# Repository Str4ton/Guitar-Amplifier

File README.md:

# Guitar-Amplifier
A guitar amplifier using the TDA2030 IC and a pre-amp using uA741CN

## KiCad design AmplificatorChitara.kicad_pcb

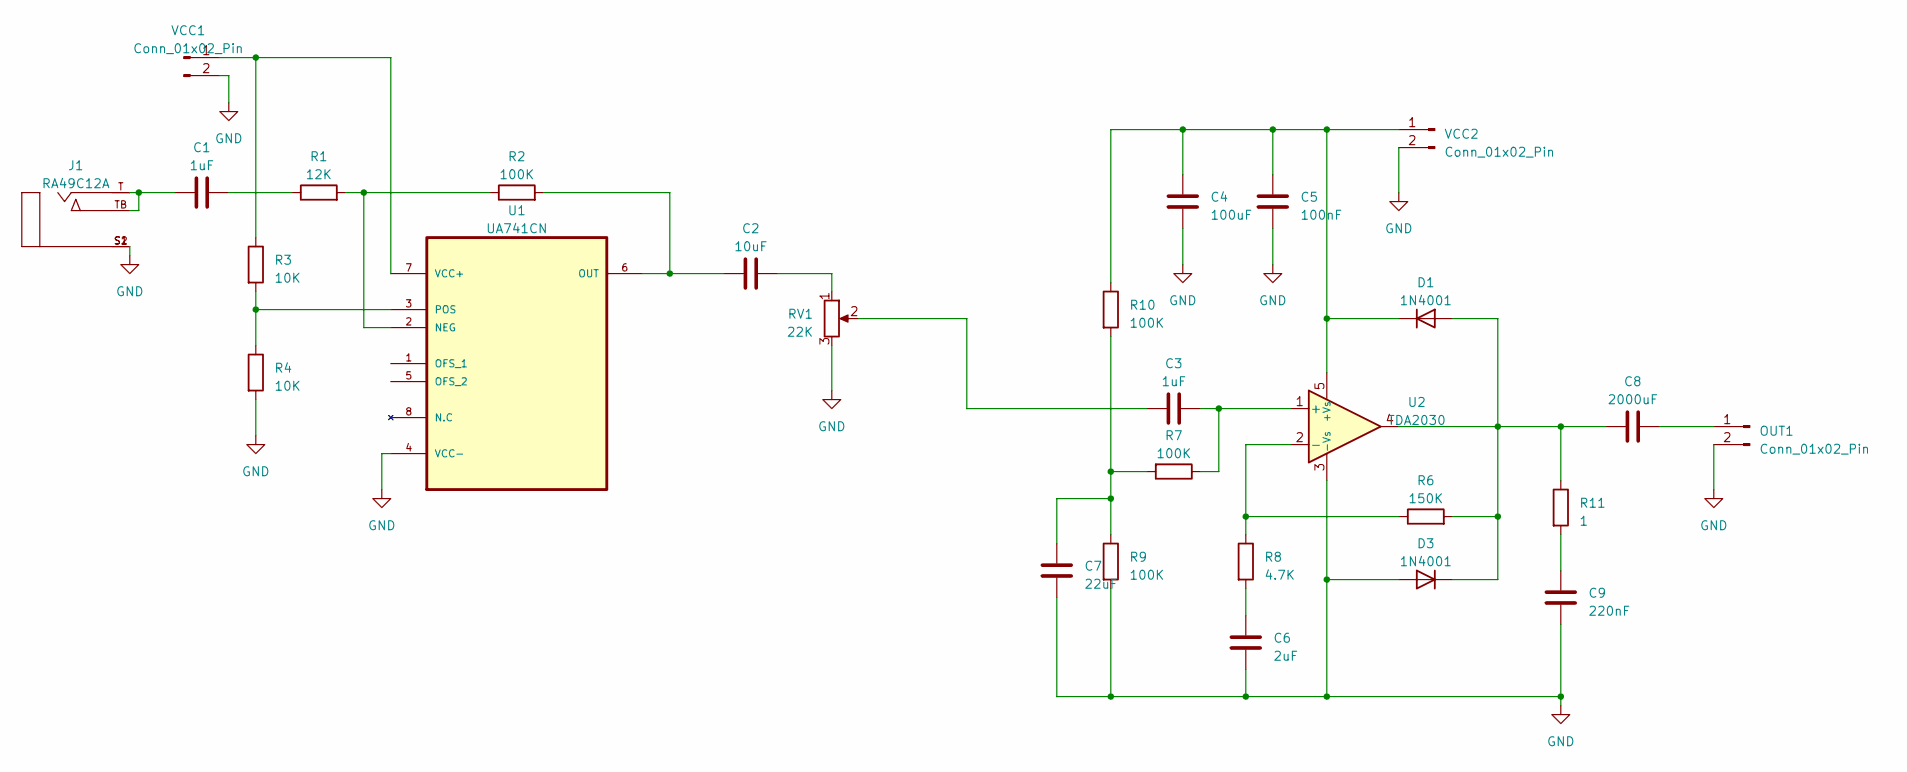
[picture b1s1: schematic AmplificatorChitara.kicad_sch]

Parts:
C1, C3: 1uF; CP_Radial_D10.0mm_P3.50mm
C2: 10uF; CP_Radial_D10.0mm_P3.50mm
C4: 100uF; CP_Radial_D10.0mm_P3.50mm
C5: 100nF; CP_Radial_D10.0mm_P3.50mm
C6: 2uF; CP_Radial_D10.0mm_P3.50mm
C7: 22uF; CP_Radial_D10.0mm_P3.50mm
C8: 2000uF; CP_Radial_D10.0mm_P3.50mm
C9: 220nF; CP_Radial_D10.0mm_P3.50mm
D1, D3: 1N4001; D_DO-41_SOD81_P10.16mm_Horizontal
J1: RA49C12A; SWITCHCRAFT_RA49C12A; PARTREV F
OUT1: Conn_01x02_Pin; TerminalBlock_4Ucon_1x02_P3.50mm_Vertical
R1: 12K; R_Axial_DIN0411_L9.9mm_D3.6mm_P12.70mm_Horizontal
R2, R7, R9, R10: 100K; R_Axial_DIN0411_L9.9mm_D3.6mm_P12.70mm_Horizontal
R3, R4: 10K; R_Axial_DIN0411_L9.9mm_D3.6mm_P12.70mm_Horizontal
R6: 150K; R_Axial_DIN0411_L9.9mm_D3.6mm_P12.70mm_Horizontal
R8: 4.7K; R_Axial_DIN0411_L9.9mm_D3.6mm_P12.70mm_Horizontal
R11: 1; R_Axial_DIN0411_L9.9mm_D3.6mm_P12.70mm_Horizontal
RV1: 22K; Potentiometer_Alps_RK09K_Single_Vertical
U1: UA741CN; DIP254P762X533-8; MPN UA741CN
U2: TDA2030; TO-220-5_P3.4x3.7mm_StaggerOdd_Lead3.8mm_Vertical
VCC1, VCC2: Conn_01x02_Pin; TerminalBlock_4Ucon_1x02_P3.50mm_Vertical

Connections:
GND: C4.2, C5.2, C6.2, C7.2, C9.2, D3.2 (A), J1.S1, J1.S2, OUT1.2, R4.2, R9.2, RV1.3, U1.4 (VCC-), U2.3 (-Vs), VCC1.2, VCC2.2
unnamed: C1.1, J1.T, J1.TB
unnamed: C1.2, R1.1
unnamed: C2.2, RV1.1
unnamed: C3.1, RV1.2
unnamed: C6.1, R8.2
unnamed: C7.1, R7.2, R9.1, R10.2
unnamed: C9.1, R11.2
unnamed: C8.1, D1.2 (A), D3.1 (K), R6.2, R11.1, U2.4
unnamed: C4.1, C5.1, D1.1 (K), R10.1, U2.5 (+Vs), VCC2.1
unnamed: C8.2, OUT1.1
unnamed: R1.2, R2.1, U1.2 (NEG)
unnamed: C2.1, R2.2, U1.6 (OUT)
unnamed: R3.2, R4.1, U1.3 (POS)
unnamed: R3.1, U1.7 (VCC+), VCC1.1
unnamed: C3.2, R7.1, U2.1 (+)
unnamed: R6.1, R8.1, U2.2 (-)

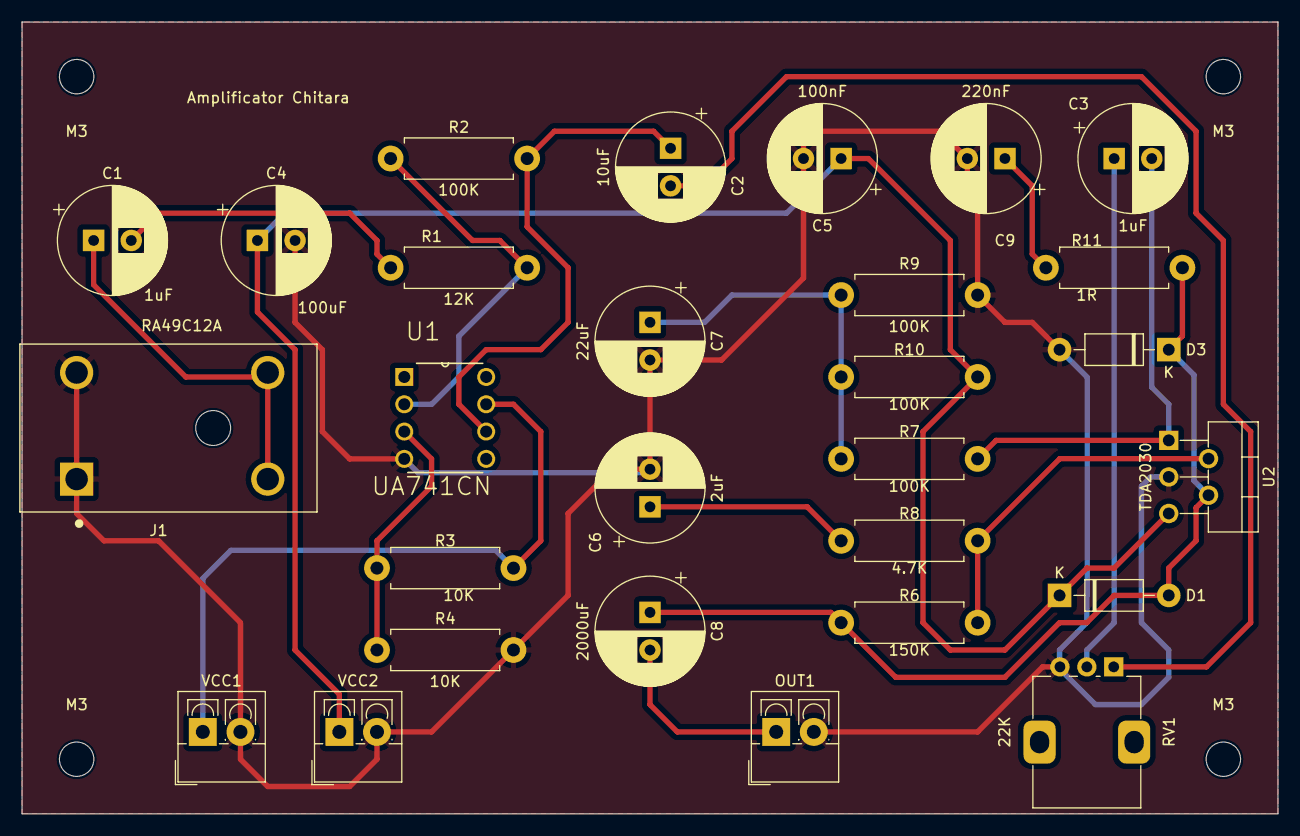
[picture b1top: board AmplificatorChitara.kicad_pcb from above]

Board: 2 copper layers, 116.8 x 73.7 mm, 32 parts (0 on the bottom side), 17 nets.

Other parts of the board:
M3, M3#2, M3#3, M3#4: MountingHole_3.2mm_M3
